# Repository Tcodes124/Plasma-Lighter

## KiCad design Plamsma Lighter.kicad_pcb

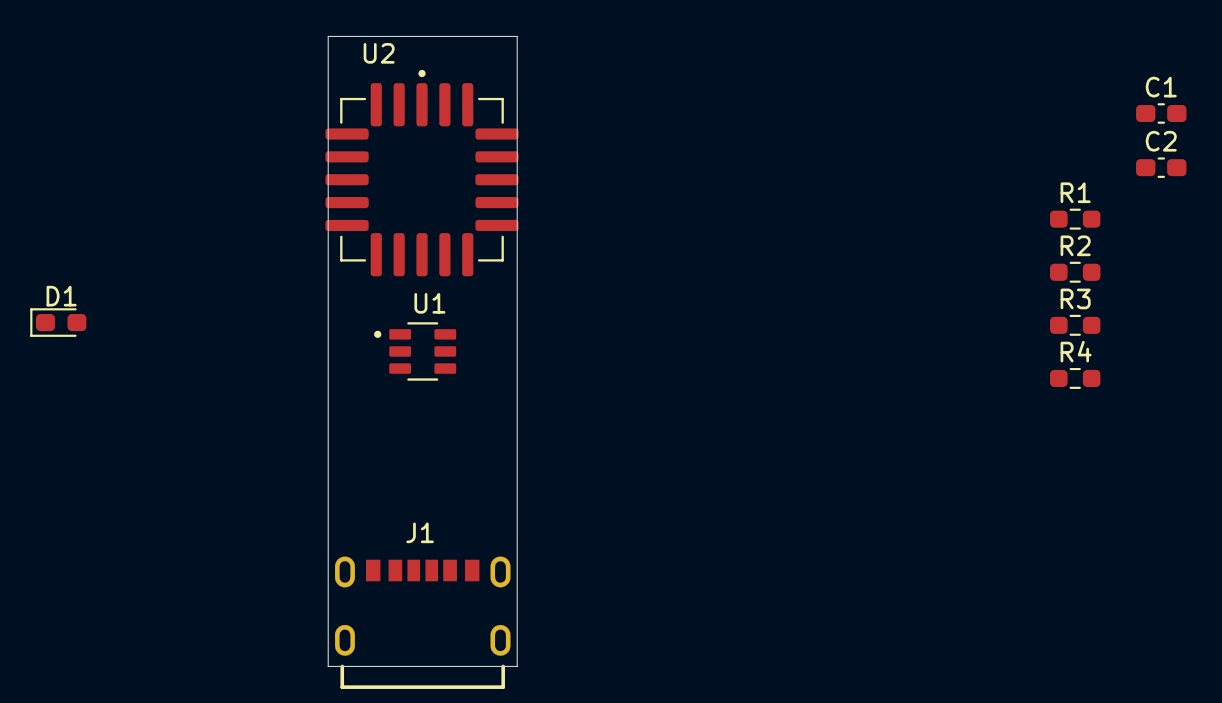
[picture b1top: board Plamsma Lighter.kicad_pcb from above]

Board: 2 copper layers, 10.5 x 35.0 mm, 10 parts (0 on the bottom side), 8 nets, no tracks yet.

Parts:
C1, C2: 1u; C_0603_1608Metric_Pad1.08x0.95mm_HandSolder
D1: LED; D_0603_1608Metric_Pad1.05x0.95mm_HandSolder
J1: USB_C_Receptacle_PowerOnly_6P; GCT_USB4125-GF-A_REVA2
R1, R2: 5.1k; R_0603_1608Metric_Pad0.98x0.95mm_HandSolder
R3: 675; R_0603_1608Metric_Pad0.98x0.95mm_HandSolder
R4: 1.5k; R_0603_1608Metric_Pad0.98x0.95mm_HandSolder
U1: BQ21040DBVR; SOT95P280X145-6N
U2: LM3914VX_NOPB; PLCC127P990X990X457-20N

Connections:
GND: C1.2, C2.2, J1.A12 (GND), J1.B12 (GND), J1.S1 (SHIELD), R1.2, R2.2, R3.2, U1.5 (GND)
unnamed: C2.1, R4.1, U1.2 (OUT)
unnamed: D1.2 (A), R4.2
unnamed: D1.1 (K), U1.3 (~CHG)
unnamed: J1.A5 (CC1), R2.1
unnamed: J1.B5 (CC2), R1.1
unnamed: R3.1, U1.4 (ISET)
unnamed: C1.1, J1.A9 (VBUS), J1.B9 (VBUS), U1.6 (VIN)

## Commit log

2025-06-28 Created prototype Schematic and inital documentation.
2025-06-28 Updated LICENSE
2025-07-02 Updated schematic.
2025-07-03 Finished prototype Schematic.
2025-07-05 Added lion battery level indicator to schematic.
